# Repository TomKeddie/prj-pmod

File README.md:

# prj-pmod

A collection of BSD licensed hardware designs for the PMOD form factor.

MIT licensed - see https://github.com/TomKeddie/prj-pmod/blob/master/LICENSE

## tom-prj-pmod

This is a PMOD module with a SAMD21 cpu on it to make it easy to add an ARM cpu to an fpga project.

Hardware : https://github.com/TomKeddie/prj-pmod/tree/master/hardware/pmod-samd21

Bootloader : https://github.com/TomKeddie/prj-pmod/tree/master/software/pmod-samd21

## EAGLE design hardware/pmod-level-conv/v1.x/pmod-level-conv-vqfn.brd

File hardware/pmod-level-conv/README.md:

# PMOD Level Converter

Converts up in voltage only (within specs of TXB0108).  Would be trivial to flip/reverse the connectors and hack the board to convert down.

Status : TSSOP v1.0 tested and working. TSOP v1.2 tested, changed only side of header pads. VQFN v1.3 untested.

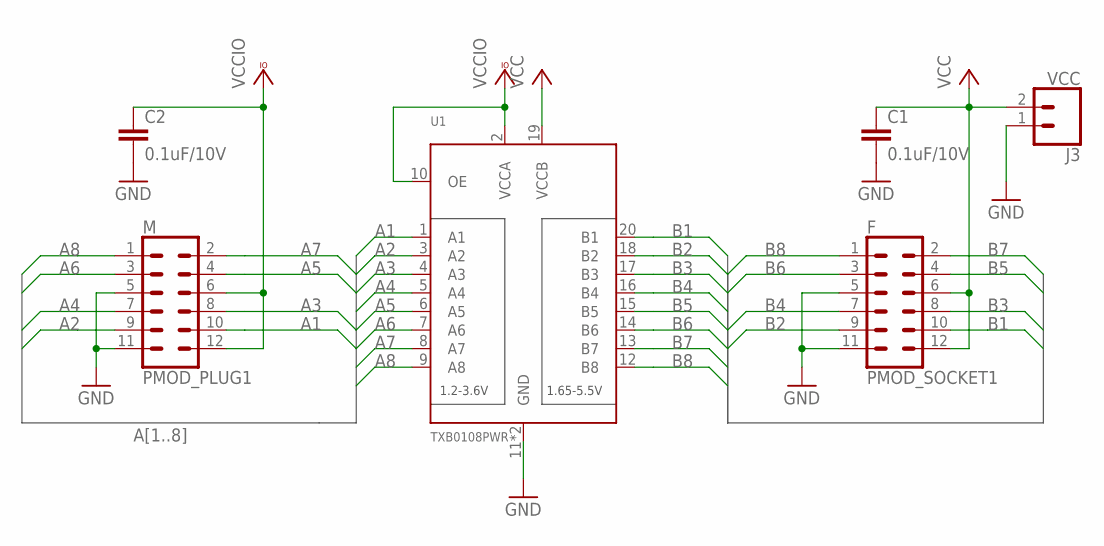
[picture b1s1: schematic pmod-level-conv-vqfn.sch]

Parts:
C1, C2: 0.1uF/10V; C0603K
F: PMOD_SOCKET1; 2X6_SMD_RA_SOCKET
J3: VCC; JST-2-SMD
M: PMOD_PLUG1; 2X6_SMD_RA_PLUG
U1: TXB0108PWR; VQFN-20

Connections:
A1: M.10, U1.1 (A1)
A2: M.9, U1.3 (A2)
A3: M.8, U1.4 (A3)
A4: M.7, U1.5 (A4)
A5: M.4, U1.6 (A5)
A6: M.3, U1.7 (A6)
A7: M.2, U1.8 (A7)
A8: M.1, U1.9 (A8)
B1: F.10, U1.20 (B1)
B2: F.9, U1.18 (B2)
B3: F.8, U1.17 (B3)
B4: F.7, U1.16 (B4)
B5: F.4, U1.15 (B5)
B6: F.3, U1.14 (B6)
B7: F.2, U1.13 (B7)
B8: F.1, U1.12 (B8)
GND: C1.2, C2.2, F.5, F.11, J3.1 (2), M.5, M.11, U1.11 (GND), U1.PAD (GND)
VCC: C1.1, F.6, F.12, J3.2 (1), U1.19 (VCCB)
VCCIO: C2.1, M.6, M.12, U1.2 (VCCA), U1.10 (OE)

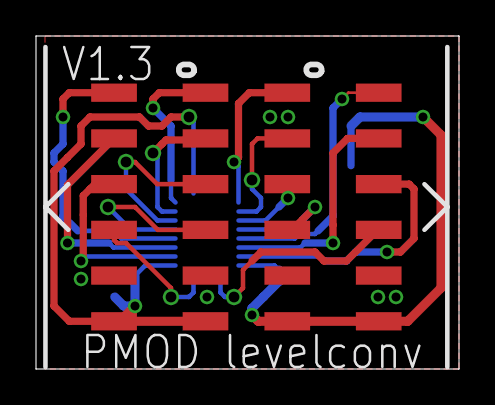
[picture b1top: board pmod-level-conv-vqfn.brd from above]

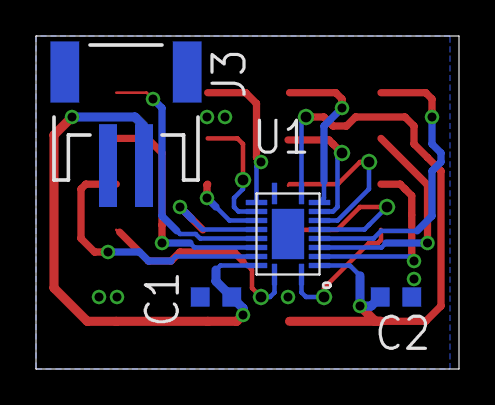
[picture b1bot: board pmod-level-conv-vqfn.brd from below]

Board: 2 copper layers, 23.5 x 18.5 mm, 6 parts (4 on the bottom side), 19 nets.

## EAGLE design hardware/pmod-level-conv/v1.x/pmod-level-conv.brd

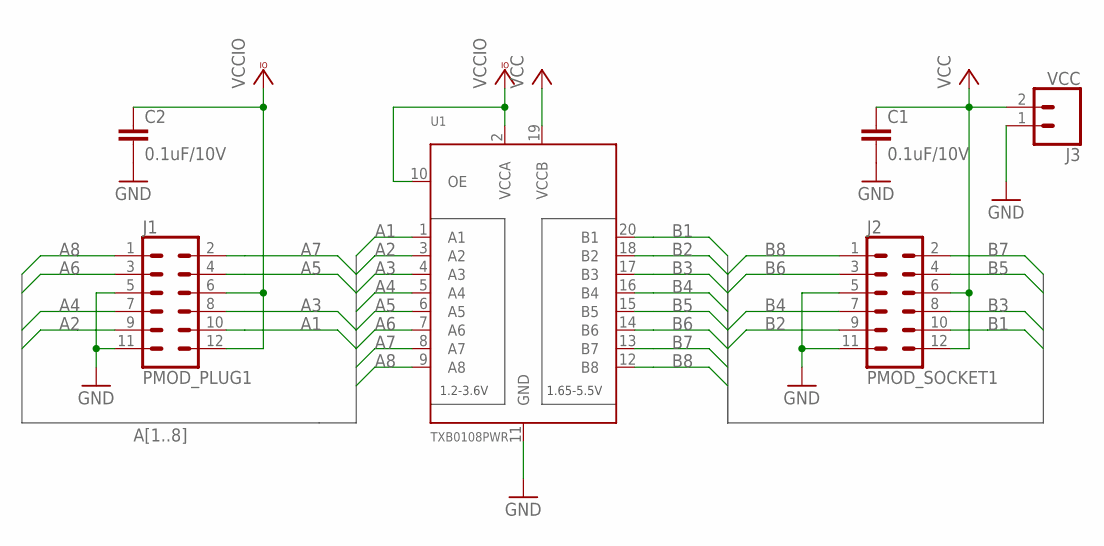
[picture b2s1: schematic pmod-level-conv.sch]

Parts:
C1, C2: 0.1uF/10V; C0603K
J1: PMOD_PLUG1; 2X6_SMD_RA_PLUG
J2: PMOD_SOCKET1; 2X6_SMD_RA_SOCKET
J3: VCC; JST-2-SMD
U1: TXB0108PWR; TSSOP20

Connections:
A1: J1.10, U1.1 (A1)
A2: J1.9, U1.3 (A2)
A3: J1.8, U1.4 (A3)
A4: J1.7, U1.5 (A4)
A5: J1.4, U1.6 (A5)
A6: J1.3, U1.7 (A6)
A7: J1.2, U1.8 (A7)
A8: J1.1, U1.9 (A8)
B1: J2.10, U1.20 (B1)
B2: J2.9, U1.18 (B2)
B3: J2.8, U1.17 (B3)
B4: J2.7, U1.16 (B4)
B5: J2.4, U1.15 (B5)
B6: J2.3, U1.14 (B6)
B7: J2.2, U1.13 (B7)
B8: J2.1, U1.12 (B8)
GND: C1.2, C2.2, J1.5, J1.11, J2.5, J2.11, J3.1 (2), U1.11 (GND)
VCC: C1.1, J2.6, J2.12, J3.2 (1), U1.19 (VCCB)
VCCIO: C2.1, J1.6, J1.12, U1.2 (VCCA), U1.10 (OE)

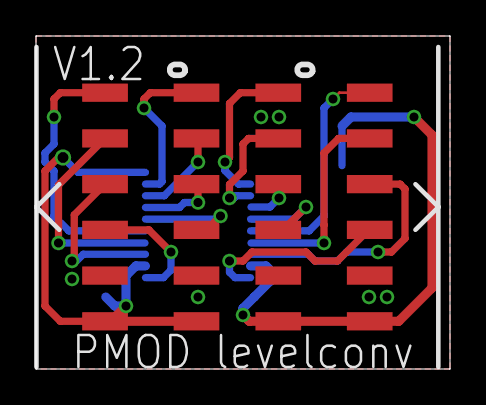
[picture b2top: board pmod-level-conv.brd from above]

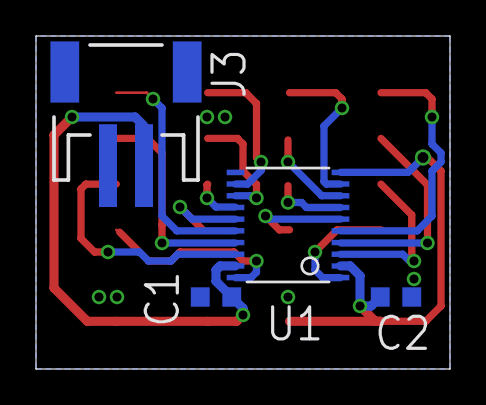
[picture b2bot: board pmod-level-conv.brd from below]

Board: 2 copper layers, 23.0 x 18.5 mm, 6 parts (4 on the bottom side), 19 nets.

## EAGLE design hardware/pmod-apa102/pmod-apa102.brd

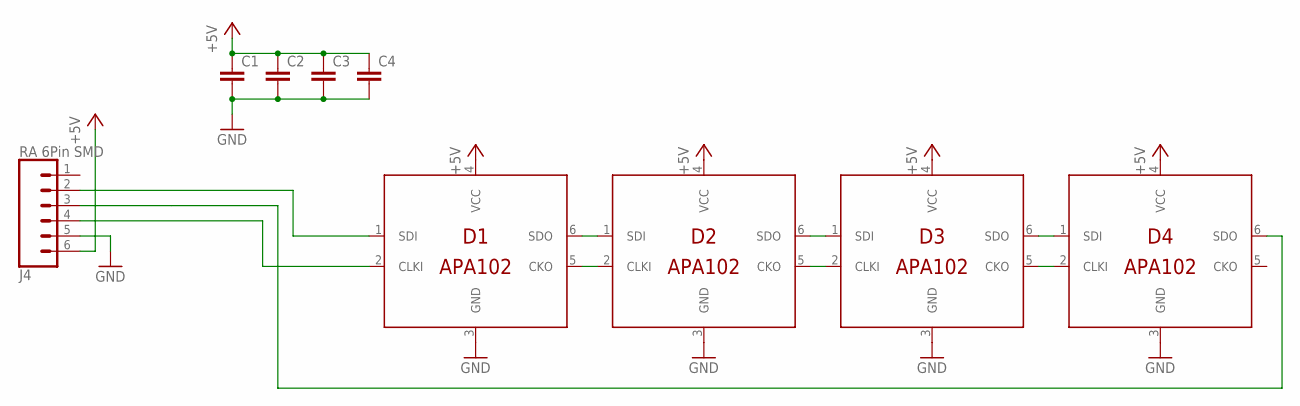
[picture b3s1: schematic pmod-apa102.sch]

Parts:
C1, C2, C3, C4: C-EUC0805K; C0805K
D1, D2, D3, D4: APA102; RGBLED5050
J4: RA 6Pin SMD; 1X06-SMD_RA_MALE

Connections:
+5V: C1.1, C2.1, C3.1, C4.1, D1.4 (VCC), D2.4 (VCC), D3.4 (VCC), D4.4 (VCC), J4.6
CLKI2: D1.5 (CKO), D2.2 (CLKI)
CLKI3: D2.5 (CKO), D3.2 (CLKI)
CLKI4: D3.5 (CKO), D4.2 (CLKI)
GND: C1.2, C2.2, C3.2, C4.2, D1.3 (GND), D2.3 (GND), D3.3 (GND), D4.3 (GND), J4.5
MISO: D4.6 (SDO), J4.3
MOSI: D1.1 (SDI), J4.2
SCK: D1.2 (CLKI), J4.4
SDI2: D1.6 (SDO), D2.1 (SDI)
SDI3: D2.6 (SDO), D3.1 (SDI)
SDI4: D3.6 (SDO), D4.1 (SDI)

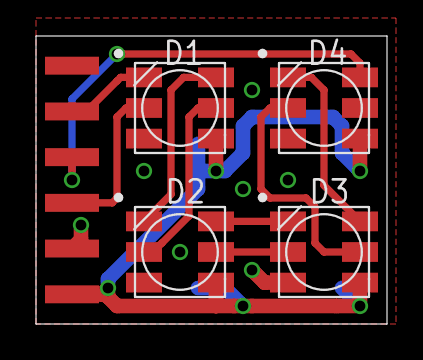
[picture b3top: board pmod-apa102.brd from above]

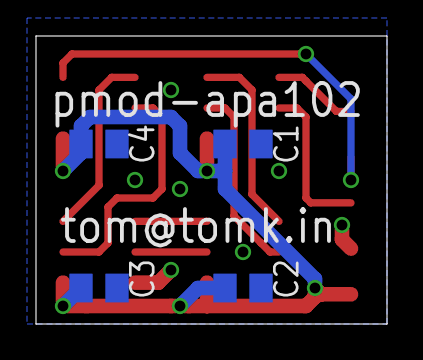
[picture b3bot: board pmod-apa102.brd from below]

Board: 2 copper layers, 19.5 x 16.0 mm, 9 parts (4 on the bottom side), 11 nets.

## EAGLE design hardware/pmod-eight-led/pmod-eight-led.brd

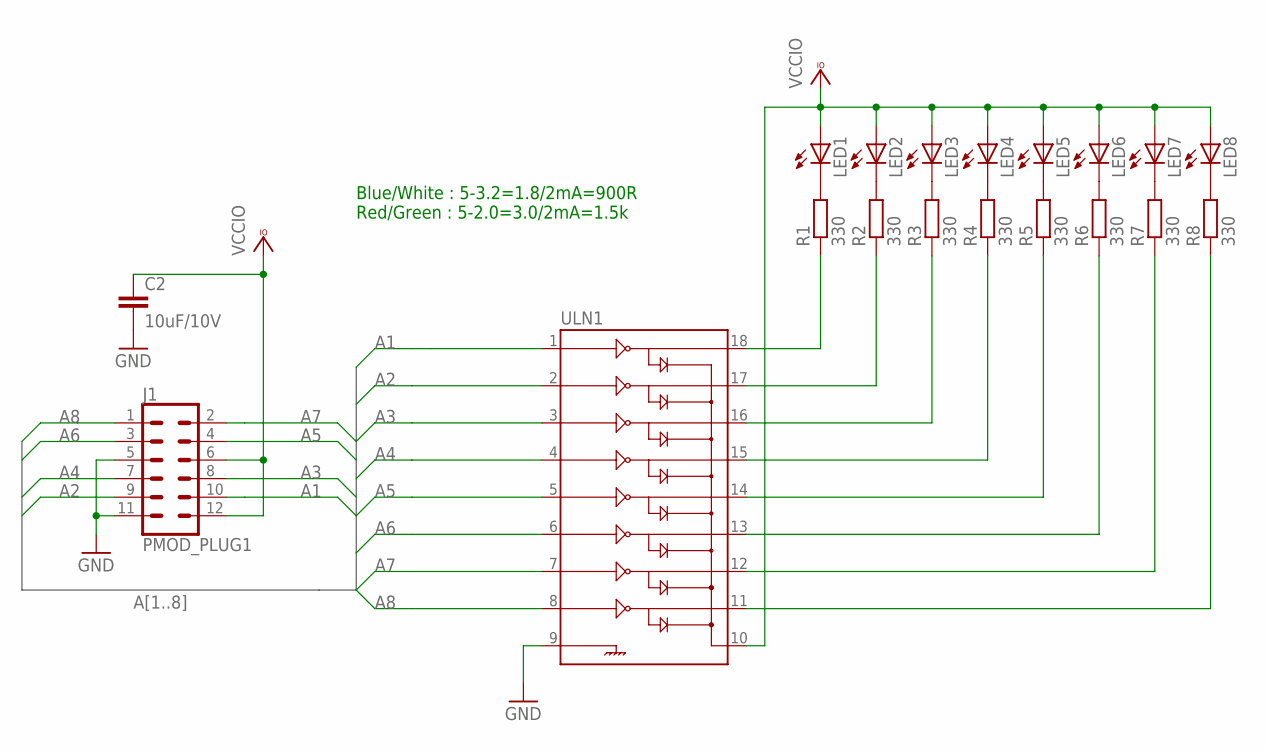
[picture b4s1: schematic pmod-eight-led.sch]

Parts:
C2: 10uF/10V; C0805K
J1: PMOD_PLUG1; 2X6_SMD_RA_PLUG
LED1, LED2, LED3, LED4, LED5, LED6, LED7, LED8: LED0603; LED-603
R1, R2, R3, R4, R5, R6, R7, R8: 330; R0805W
ULN1: ULN2803SOICW; SO18L

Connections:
A1: J1.10, ULN1.1
A2: J1.9, ULN1.2
A3: J1.8, ULN1.3
A4: J1.7, ULN1.4
A5: J1.4, ULN1.5
A6: J1.3, ULN1.6
A7: J1.2, ULN1.7
A8: J1.1, ULN1.8
GND: C2.2, J1.5, J1.11, ULN1.9
LED1: R1.1, ULN1.18
LED2: R2.1, ULN1.17
LED3: R3.1, ULN1.16
LED4: R4.1, ULN1.15
LED5: R5.1, ULN1.14
LED6: R6.1, ULN1.13
LED7: R7.1, ULN1.12
LED8: R8.1, ULN1.11
unnamed: LED1.C, R1.2
unnamed: LED2.C, R2.2
unnamed: LED3.C, R3.2
unnamed: LED4.C, R4.2
unnamed: LED5.C, R5.2
unnamed: LED6.C, R6.2
unnamed: LED7.C, R7.2
unnamed: LED8.C, R8.2
VCCIO: C2.1, J1.6, J1.12, LED1.A, LED2.A, LED3.A, LED4.A, LED5.A, LED6.A, LED7.A, LED8.A, ULN1.10

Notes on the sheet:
Blue/White : 5-3.2=1.8/2mA=900R Red/Green : 5-2.0=3.0/2mA=1.5k

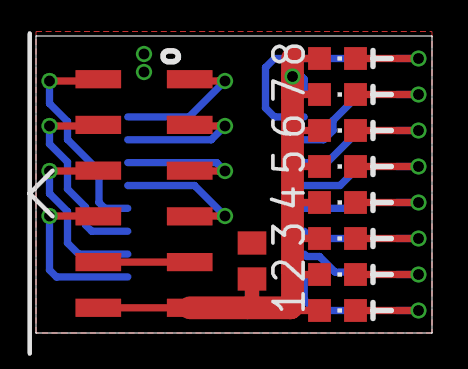
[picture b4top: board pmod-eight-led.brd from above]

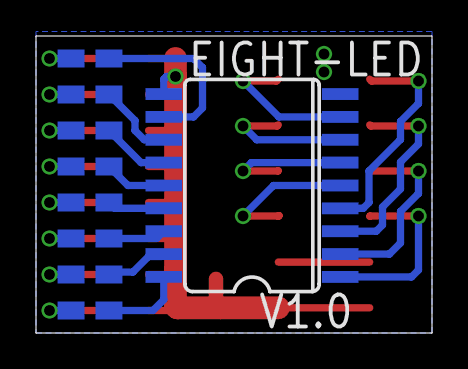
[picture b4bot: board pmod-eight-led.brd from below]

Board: 2 copper layers, 22.0 x 16.5 mm, 19 parts (9 on the bottom side), 26 nets.

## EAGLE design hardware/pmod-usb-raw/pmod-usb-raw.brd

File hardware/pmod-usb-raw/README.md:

# USB PMOD

This is a raw USB pmod with an LED and pullup.  It's designed to work with
the TinyFPGA Bootloader but could be used for any project that bitbangs usb.

It has both USB Micro and USB Mini, you only need one or the other.  It also has power LEDs for both the USB connection and the PMOD connection.  On the underside it has a LED driven by one of the PMOD pins.

See the bootloader at https://github.com/tinyfpga/TinyFPGA-Bootloader

Order at oshpark via https://oshpark.com/shared_projects/UDlBSFXa

BOM at octopart via https://octopart.com/bom-tool/BNyMEAgK (I don't have the part number for the micro usb, please let me know if you find it)

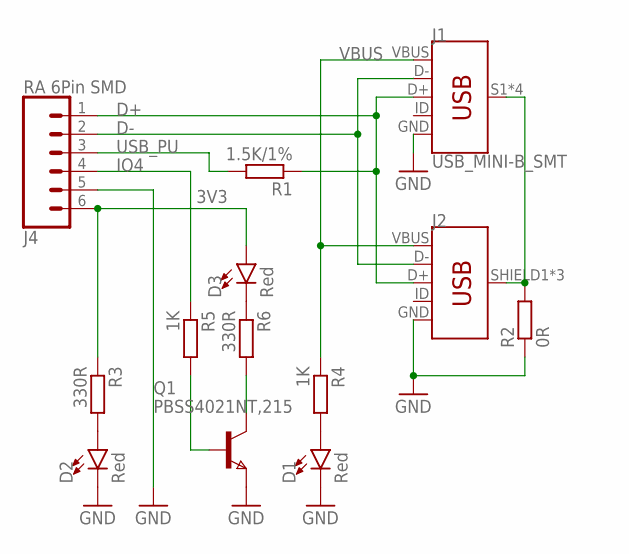
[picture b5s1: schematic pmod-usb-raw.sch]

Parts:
D1, D2, D3: Red; LED-0603
J1: USB_MINI-B_SMT; USB-MINIB
J2: USB_MICRO-B_FEMALE-SMT; USB-B-MICRO-SMD
J4: RA 6Pin SMD; 1X06-SMD_RA_MALE
Q1: PBSS4021NT,215; SOT23
R1: 1.5K/1%; R0603
R2: 0R; R0603
R3, R6: 330R; R0603
R4, R5: 1K; R0603

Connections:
3V3: D3.A, J4.6, R3.1
D+: J1.D+, J2.D+, J4.1, R1.1
D-: J1.D-, J2.D-, J4.2
GND: D1.C, D2.C, J1.GND, J2.GND, J4.5, Q1.2 (E), R2.1
IO4: J4.4, R5.1
unnamed: D2.A, R3.2
unnamed: D1.A, R4.2
unnamed: Q1.1 (B), R5.2
unnamed: D3.C, R6.1
unnamed: Q1.3 (C), R6.2
SHIELD: J1.S1 (SHIELD), J1.S2 (SHIELD), J1.S3 (SHIELD), J1.S4 (SHIELD), J2.SHIELD1 (SHIELD), J2.SHIELD2 (SHIELD), J2.SHIELD3 (SHIELD), R2.2
USB_PU: J4.3, R1.2
VBUS: J1.VBUS, J2.VBUS, R4.1

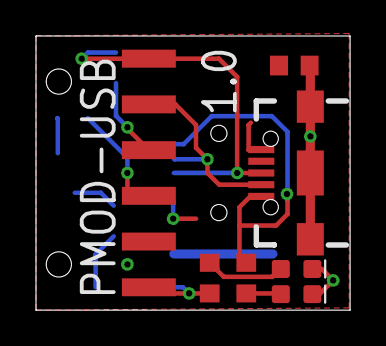
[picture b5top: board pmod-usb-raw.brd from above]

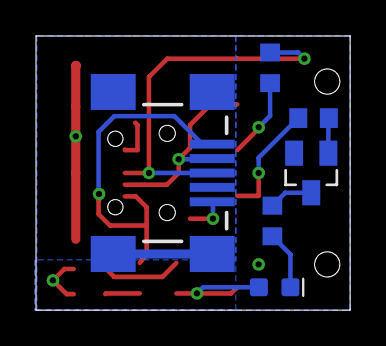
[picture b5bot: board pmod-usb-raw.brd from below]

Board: 2 copper layers, 17.4 x 15.2 mm, 13 parts (6 on the bottom side), 13 nets.

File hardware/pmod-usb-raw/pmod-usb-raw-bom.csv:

"Qty";"Value";"Device";"Package";"Parts";"Description";"PROD_ID";"SF_ID";"SPICEPREFIX";"VALUE";
"1";"";"USB_MICRO-B_FEMALE-SMT";"USB-B-MICRO-SMD";"J2";"USB Type Micro-B Connector";"CONN-11752";"";"";"";
"1";"0R";"R-EU_R0603";"R0603";"R2";"RESISTOR, European symbol";"";"";"R";"";
"1";"1.5K/1%";"R-EU_R0603";"R0603";"R1";"RESISTOR, European symbol";"";"";"R";"";
"2";"1K";"R-EU_R0603";"R0603";"R4, R5";"RESISTOR, European symbol";"";"";"R";"";
"2";"330R";"R-EU_R0603";"R0603";"R3, R6";"RESISTOR, European symbol";"";"";"R";"";
"1";"PBSS4021NT,215";"PBSS4021NT,215";"SOT23";"Q1";"";"";"";"";"";
"1";"RA 6Pin SMD";"CONN_06SMD";"1X06-SMD_RA_MALE";"J4";"Multi connection point. Often used as Generic Header-pin footprint for 0.1 inch spaced/style header connections";"CONN-08971";"";"";"RA 6Pin SMD";
"3";"Red";"LED-RED0603-SMART";"LED-0603";"D1, D2, D3";"Red SMD LED";"DIO-11154";"";"";"Red";
"1";"USB_MINI-B_SMT";"USB_MINI-B_SMT";"USB-MINIB";"J1";"USB type Mini-B Connector";"CONN-08193";"PRT-00587";"";"";

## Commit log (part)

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2018-05-27 PMOD USB RAW for tinyfpga bootloader - rev 1.0 as sent to oshpark
2018-06-20 Added README
2018-06-20 Add oshpark link
2018-06-20 Added images of USB PMOD
2018-06-20 Added BOM for usb pmod
2018-06-20 Updated usb README to add octopart
2018-06-20 Add image for usb raw pmod
2018-06-20 Add image to USB readme
2018-06-20 Update README to show image
2018-06-20 Fix typo in README
2018-06-24 pmod level converter added (v1.0 as sent to oshpark)
2018-07-26 Update level conv pcb to rev 1.1 - fix smd pad sizes for pmod connectors
2018-07-27 Eight LED PMOD as submitted to OSH Park
2018-08-06 Added APA102 PMOD board
2018-08-06 APA102 PMD as submitted to Oshpark (minor silk fixups)
2018-08-13 pmod-level-conv : fixed NC OE
2018-10-28 Added VQFN version of pmod level converter
2018-10-28 Added eagle samd5x5 schematic
2018-10-30 First pass at kicad schematic for samd21 pmod
2018-10-31 Add kicad backups to gitignore
2018-10-31 First pass at routing of samd21 pmod, power yet to be done
2018-10-31 PCB fully routed with DRC errors ignored - oshpark doesn't like the slots in the usb connector - need to check FET pinout
2018-11-26 pcb as submitted to oshpark
2018-11-26 Added pmod-samd21 openocd config
2018-11-26 Add samd bootloader from Arduino for pmod-samd21
2018-11-26 Add sam_ba build for pmod-samd21 with led on B23
2018-11-26 Fix path to sam_ba binary
2018-12-05 pmod-samd21 : Fixed edge cuts for panelisation with plated slots
2018-12-07 pmod-samd21 - added missing usb C resistors - generated gerbers relative to aux origin
2018-12-07 pmod-samd21 : rename to create usb-c variant
2018-12-07 pmod-samd : clone usbc variant to make microusb variant
2018-12-09 SAMD21 PMOD microusb version
2018-12-09 pmod-samd21 : add missing gerbers for usbu variant
2018-12-09 pmod-samd21 : Move usbu gerbers to separate folder
2018-12-31 Updated led pmod
2019-01-16 Added pcb for micro usb samd21 pmod
2019-01-16 pmod-samd21 : routed and ready for fab
2019-03-20 Add ibom for pmod-samd21-usbu
2019-03-20 Create LICENSE
2019-03-20 pmod-samd21-usbu-pth : as sent to fab
2019-03-20 gerber-usbu-pth : add missing drill file
2019-03-20 Update README.md
    Add Arduino digital and analog pin numbers
2019-03-20 Update README.md
    Add arduino aliases
2019-03-21 Update README.md
    Add notes on power supply.
2019-04-25 pmod-samd21 : added prj-fpga submodule
2019-04-25 pmod-samd21 : changes for seeed studio opl fabrication
2019-04-25 Add PTC pin details to README.
2019-04-26 Update README.md
    Add pin details for SPI and PTC
2019-04-26 pmod-samd21: update to use pidcodes PID, fix manufacturer name (use BOARD_ID=pmod_samd21 NAME=pmod_samd21 make)
2019-04-26 pmod-samd21: first pass at hdl example for pmod-samd21-midi
2019-04-26 pmod-samd21 : minor updates
2019-05-05 pmod-usb-analyser-openvizla : first pass at usb analyser pmod
2019-05-05 pmod-usb-analyser-openvizla : remove refs from silk
2019-08-28 Add pmod-sao : shitty addon pmod
2019-09-02 Added pmod-fan5702 as submitted to oshpark
2019-09-02 Updated submodule tom-kicad
2019-09-08 Move pmod-samd21-usbu-pth to separate project
2019-09-08 Fix IO assignments on PMOD so both i2c and spi work
2019-09-08 Add kicad specific gitignore, move pmod-samd21-usbu-pth to subdir
2019-09-09 pmod-samd21-usbu-pth : fix pin assignments to make i2c and spi viable
2019-09-10 pmod-samd21: routed pth version with spi/i2c compatibile addressing
2019-09-11 pmod-samd21: Fix PCB rev in silk
2019-09-26 pmod-samd21-usbc: move files to separate directory
2019-10-06 pmod-sao : added images
2019-10-06 pmod-level-conv : add doco
2019-10-16 pmod-usb-analyser-openvizla: add missing files, fix library references
2019-10-16 pmod-usb-analyser-openvizla: move old pcb to qfn suibdirectory ready to create BGA version
2019-10-19 pmod-usb-analyser-openvizla: add schematic image
2019-11-09 pmod-level-conv: restructure files
2019-11-09 pmod-level-conv: add v2.x
2019-12-13 pmod-ftdi : v1.0
2020-01-11 pmod-ftdi: rev 1.1 - fix ft230xs package
2020-01-11 pmod-ftdi: switch to correct symbol for FT230XS
2020-02-05 pmod-usb-analyser: feedback from ktempkin - move VBAT to 5V - moved 3.3V to LDO
2020-02-05 Submodule update
2020-02-05 pmod-ftdi : as built
2020-02-05 update gitignore
2020-04-07 pmod-16x16led: add 16x16 led matrix pmod
2020-04-08 pmod-16x16led: Apr2020 version as submitted to oshpark
2020-11-22 hardware: update tom-kicad submodule to latest
2020-11-22 pmod-swd: Nov2020 release
2020-11-27 Update tom-kicad submodule
2020-12-08 pmod-rgb-led: first steps of an RGB led matrix
2020-12-08 pmod-rgb-led: add bus name to fix erc errors
2020-12-08 pmod-rgb-led: update tom-kicad to use local copy
2020-12-08 Add missed files
2021-03-12 pmod-ulpi-adapter: adapter to connect cheap ulpi board to pmod
2021-03-12 pmod-ulpi-adapter: Mar2021A release, swapped pmod connectors for more clock option
2022-11-21 hardware/pmod-button: new design
2023-11-25 pmod-level-conv-2: new design

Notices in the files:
parts and their libraries:
SparkFun-IC-Special-Function: Licensing: Creative Commons ShareAlike 4.0 International - https://creativecommons.org/licenses/by-sa/4.0
